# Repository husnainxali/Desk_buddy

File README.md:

# Desk_buddy
A desk companion that you can place on your desk, which displays the time, starts timers, and provides room temperature and weather forecasts through voice commands.

## Description
So I made this because i saw multiple people on youtube making their own desk buddy 

So I also wanted to make one that can tell time set timers,show weather,Check room temprature and humidity 
I also wanted it to act as a chat Bot and added microphone and Speaker into the PCB design But because of my limited knowledge I couldn't add chat bot feature but I will be adding them soon 
The PCb has Both the microphone and speaker ports in it so if u want to add the chat bot u can add it by writing your own firmware  

### Screenshots
- *PCB*

- *Case*

-*Explode View* 

- *Schematic*
 
  **[Schematics.pdf](Render/Schematics.pdf)**  

## BOM

Full parts list with quantities and costs: **[BOM.csv](BOM.csv)**
        
## Getting Started

- First of all download the Gerber files from production Folder
- ORder your PCb using those Gerber files
- U can also add changes to Pcb by downloading KIcad files From PCB folder
- After that solder your parts onto the pcb and connect your Oled screen with jumper wires
  
### Dependencies

- *Arduino IDE*
- *ESP board instalation in Arduino IDE*
- *USB Cable*

### Installing
- Download the **[Firmware.ino](Firmware.ino)**
- Open it in Arduino IDE

### Executing program

- *Connect your ESP board with pc using a USB cable *

- *Select your ESP as the board in Arduino IDE*

- *Click the Upload(arrow) button to flash your Esp board with firmware*

## License

This project is licensed under the [MIT License](LICENSE).

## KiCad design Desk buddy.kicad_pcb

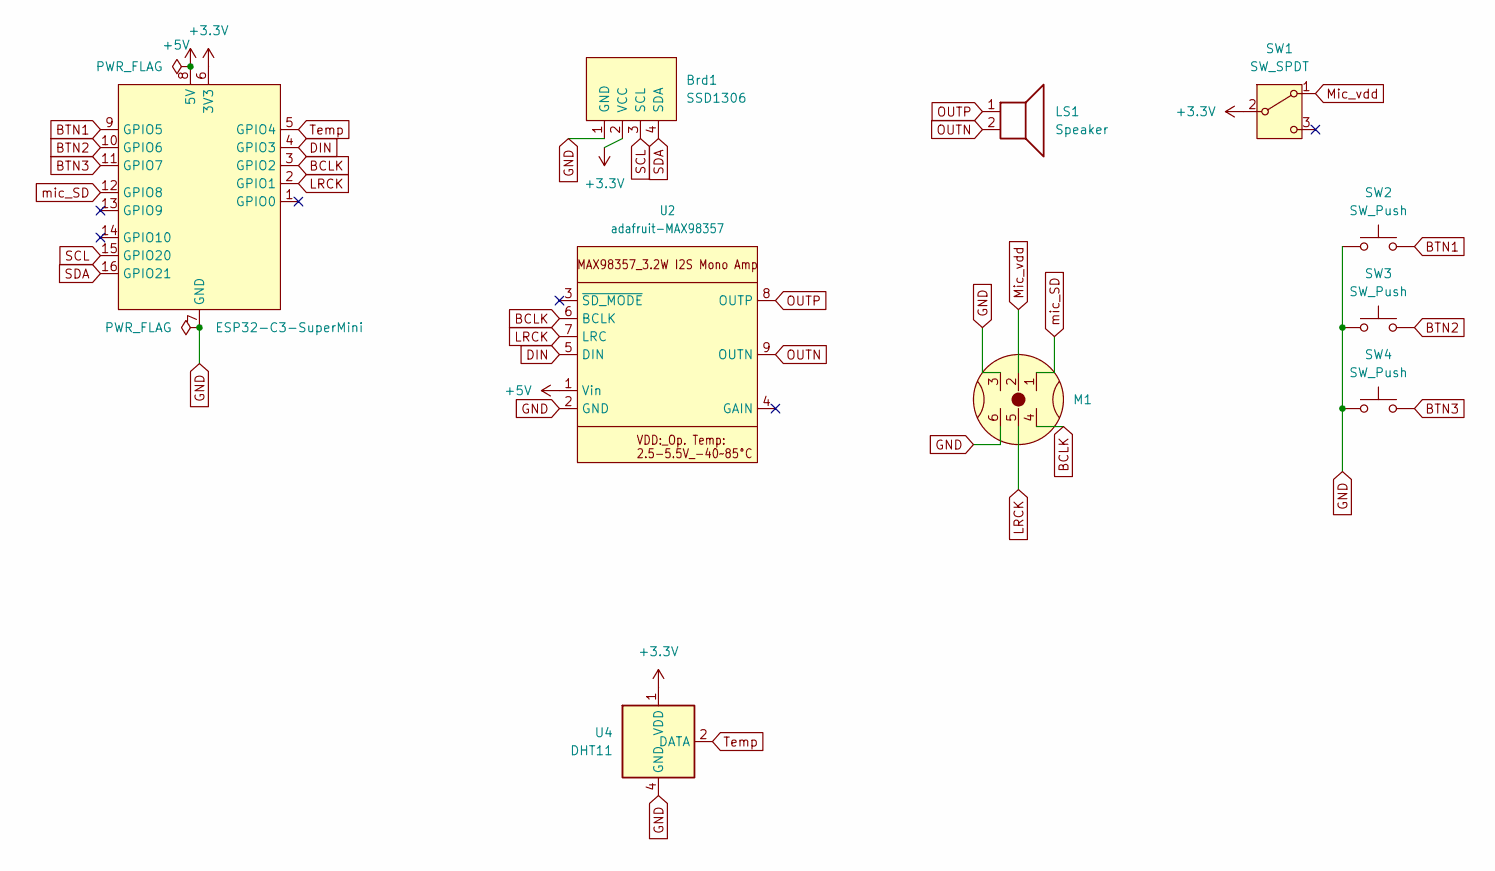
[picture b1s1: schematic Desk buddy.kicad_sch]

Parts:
Brd1: SSD1306; PinHeader_1x04_P2.54mm_Vertical
LS1: Speaker; PinHeader_1x02_P2.54mm_Vertical
M1: PinSocket_1x06_P2.54mm_Vertical
SW1: SW_SPDT; SW_Slide_SPDT_Straight_CK_OS102011MS2Q
SW2, SW3, SW4: SW_Push; SW_PUSH_6mm
U1: ESP32-C3-SuperMini
U2: adafruit-MAX98357
U4: DHT11; Aosong_DHT11_5.5x12.0_P2.54mm

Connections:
+3.3V: Brd1.2 (VCC), SW1.2 (B), U1.6 (3V3), U4.1 (VDD)
+5V: U1.8 (5V), U2.1 (Vin)
BCLK: M1.4, U1.3 (GPIO2), U2.6 (BCLK)
BTN1: SW2.2, U1.9 (GPIO5)
BTN2: SW3.2, U1.10 (GPIO6)
BTN3: SW4.2, U1.11 (GPIO7)
DIN: U1.4 (GPIO3), U2.5 (DIN)
GND: Brd1.1 (GND), M1.3, M1.6, SW2.1, SW3.1, SW4.1, U1.7 (GND), U2.2 (GND), U4.4 (GND)
LRCK: M1.5, U1.2 (GPIO1), U2.7 (LRC)
Mic_vdd: M1.2, SW1.1 (A)
OUTN: LS1.2, U2.9 (OUTN)
OUTP: LS1.1, U2.8 (OUTP)
SCL: Brd1.3 (SCL), U1.15 (GPIO20)
SDA: Brd1.4 (SDA), U1.16 (GPIO21)
Temp: U1.5 (GPIO4), U4.2 (DATA)
mic_SD: M1.1, U1.12 (GPIO8)

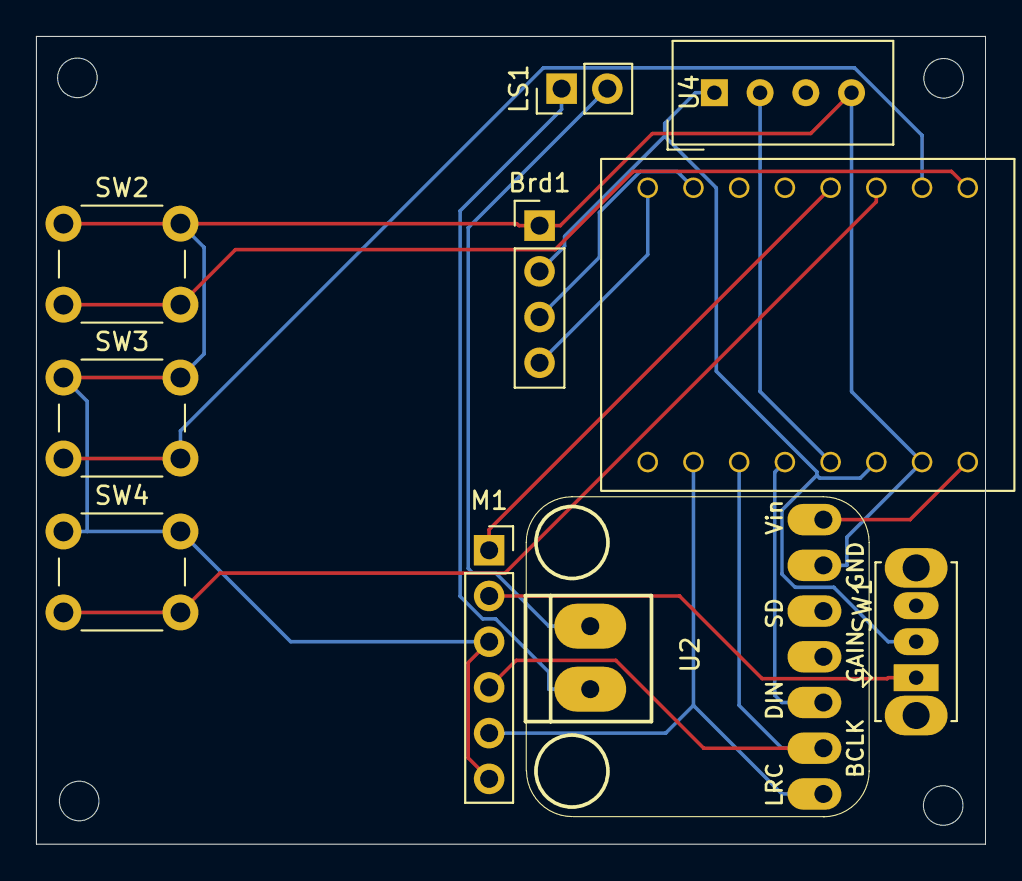
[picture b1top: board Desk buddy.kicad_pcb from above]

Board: 2 copper layers, 52.7 x 44.9 mm, 10 parts (0 on the bottom side), 16 nets.
